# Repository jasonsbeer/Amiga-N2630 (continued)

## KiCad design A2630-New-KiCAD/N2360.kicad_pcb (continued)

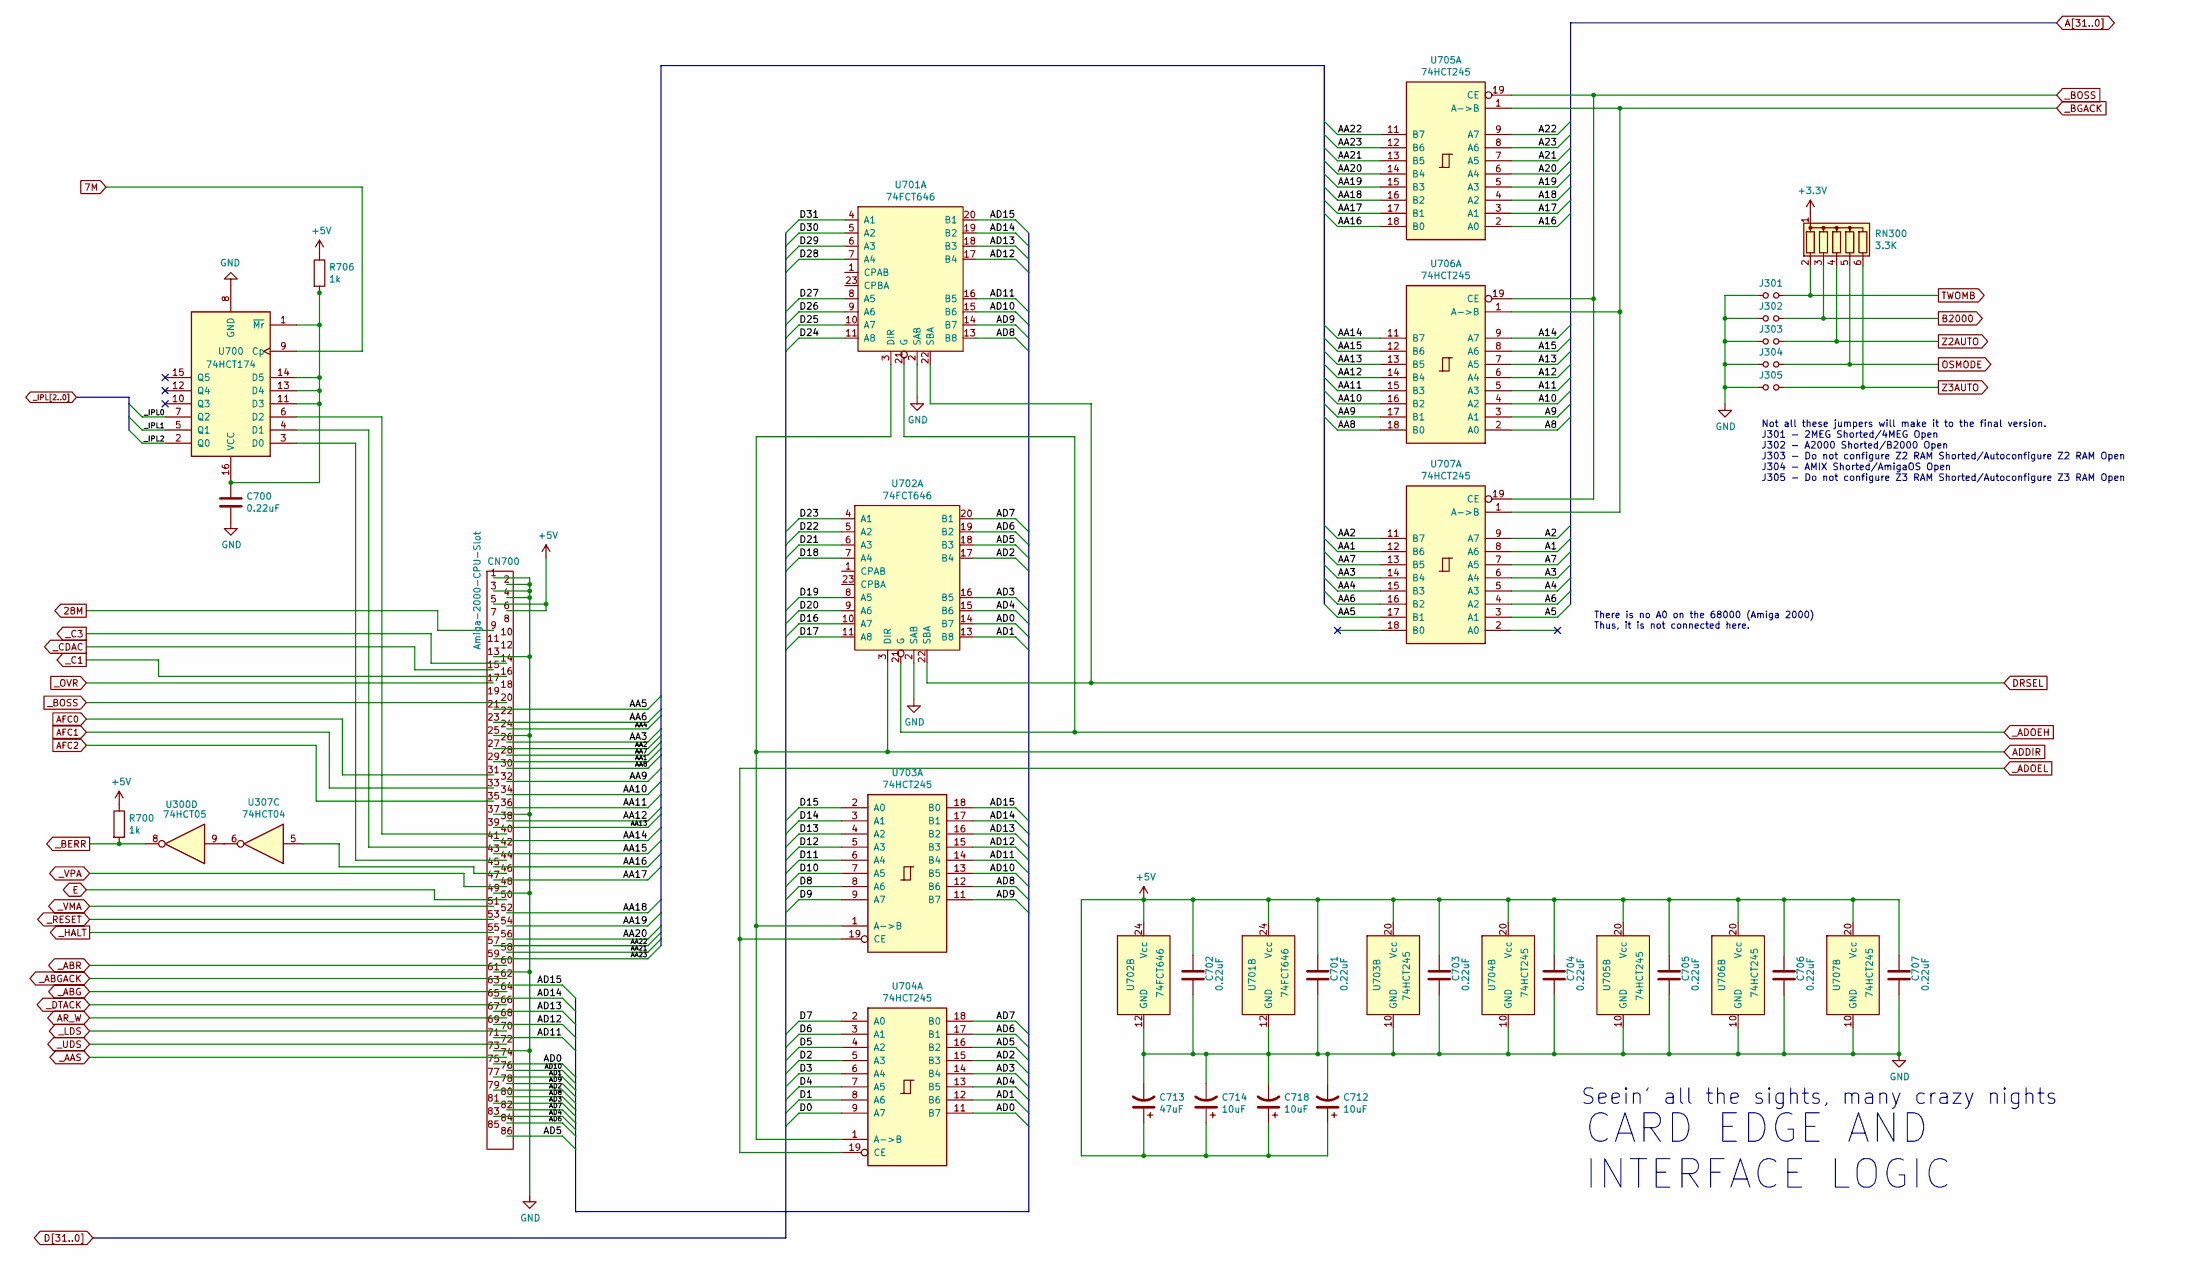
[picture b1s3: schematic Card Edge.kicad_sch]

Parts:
C700, C701, C702, C703, C704, C705, C706, C707: 0.22uF; C_0805_2012Metric
C712, C714, C718: 10uF; CP_Radial_D5.0mm_P2.00mm
C713: 47uF; CP_Radial_D5.0mm_P2.00mm
CN700: Amiga-2000-CPU-Slot; A2000_CPUSLOT_MALE
J301, J302, J303, J304, J305: Jumper_NO_Small; PinHeader_1x02_P2.54mm_Vertical
R700, R706: 1k; R_0805_2012Metric
RN300: 3.3K; R_Array_SIP6
U300: 74HCT05; SOIC-14_3.9x8.7mm_P1.27mm
U307: 74HCT04; SOIC-14_3.9x8.7mm_P1.27mm
U700: 74HCT174; SOIC-16_3.9x9.9mm_P1.27mm
U701, U702: 74FCT646; SOIC-24W_7.5x15.4mm_P1.27mm; Digikey 296-33244-5-ND
U703, U704, U705, U706, U707: 74HCT245; SOIC-24W_7.5x15.4mm_P1.27mm

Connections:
7M: U700.9 (Cp); also elsewhere on the board
28M: CN700.9; also elsewhere on the board
+3V3: RN300.1 (common); also elsewhere on the board
/Card Edge/AA1: CN700.29, U707.12 (B6)
/Card Edge/AA2: CN700.27, U707.11 (B7)
/Card Edge/AA3: CN700.26, U707.14 (B4)
/Card Edge/AA4: CN700.24, U707.15 (B3)
/Card Edge/AA5: CN700.21, U707.17 (B1)
/Card Edge/AA6: CN700.23, U707.16 (B2)
/Card Edge/AA7: CN700.28, U707.13 (B5)
/Card Edge/AA8: CN700.30, U706.18 (B0)
/Card Edge/AA9: CN700.32, U706.17 (B1)
/Card Edge/AA10: CN700.34, U706.16 (B2)
/Card Edge/AA11: CN700.36, U706.15 (B3)
/Card Edge/AA12: CN700.38, U706.14 (B4)
/Card Edge/AA13: CN700.39, U706.13 (B5)
/Card Edge/AA14: CN700.41, U706.11 (B7)
/Card Edge/AA15: CN700.43, U706.12 (B6)
/Card Edge/AA16: CN700.45, U705.18 (B0)
/Card Edge/AA17: CN700.47, U705.17 (B1)
/Card Edge/AA18: CN700.52, U705.16 (B2)
/Card Edge/AA19: CN700.54, U705.15 (B3)
/Card Edge/AA20: CN700.56, U705.14 (B4)
/Card Edge/AA21: CN700.58, U705.13 (B5)
/Card Edge/AA22: CN700.57, U705.11 (B7)
/Card Edge/AA23: CN700.59, U705.12 (B6)
/Card Edge/AD0: CN700.75, U702.14 (B7), U704.11 (B7)
/Card Edge/AD1: CN700.77, U702.13 (B8), U704.12 (B6)
/Card Edge/AD2: CN700.79, U702.17 (B4), U704.15 (B3)
/Card Edge/AD3: CN700.81, U702.16 (B5), U704.14 (B4)
/Card Edge/AD4: CN700.83, U702.15 (B6), U704.13 (B5)
/Card Edge/AD5: CN700.86, U702.18 (B3), U704.16 (B2)
/Card Edge/AD6: CN700.84, U702.19 (B2), U704.17 (B1)
/Card Edge/AD7: CN700.82, U702.20 (B1), U704.18 (B0)
/Card Edge/AD8: CN700.80, U701.13 (B8), U703.12 (B6)
/Card Edge/AD9: CN700.78, U701.14 (B7), U703.11 (B7)
/Card Edge/AD10: CN700.76, U701.15 (B6), U703.13 (B5)
/Card Edge/AD11: CN700.71, U701.16 (B5), U703.14 (B4)
/Card Edge/AD12: CN700.69, U701.17 (B4), U703.15 (B3)
/Card Edge/AD13: CN700.67, U701.18 (B3), U703.16 (B2)
/Card Edge/AD14: CN700.65, U701.19 (B2), U703.17 (B1)
/Card Edge/AD15: CN700.63, U701.20 (B1), U703.18 (B0)
A1: U707.8 (A6); also elsewhere on the board
A2: U707.9 (A7); also elsewhere on the board
A3: U707.6 (A4); also elsewhere on the board
A4: U707.5 (A3); also elsewhere on the board
A5: U707.3 (A1); also elsewhere on the board
A6: U707.4 (A2); also elsewhere on the board
A7: U707.7 (A5); also elsewhere on the board
A8: U706.2 (A0); also elsewhere on the board
A9: U706.3 (A1); also elsewhere on the board
A10: U706.4 (A2); also elsewhere on the board
A11: U706.5 (A3); also elsewhere on the board
A12: U706.6 (A4); also elsewhere on the board
A13: U706.7 (A5); also elsewhere on the board
A14: U706.9 (A7); also elsewhere on the board
A15: U706.8 (A6); also elsewhere on the board
A16: U705.2 (A0); also elsewhere on the board
A17: U705.3 (A1); also elsewhere on the board
A18: U705.4 (A2); also elsewhere on the board
A19: U705.5 (A3); also elsewhere on the board
A20: U705.6 (A4); also elsewhere on the board
A21: U705.7 (A5); also elsewhere on the board
A22: U705.9 (A7); also elsewhere on the board
A23: U705.8 (A6); also elsewhere on the board
ADDIR: U701.3 (DIR), U702.3 (DIR), U703.1 (A->B), U704.1 (A->B); also elsewhere on the board
AFC0: CN700.31; also elsewhere on the board
AFC1: CN700.33; also elsewhere on the board
AFC2: CN700.35; also elsewhere on the board
AR_W: CN700.68; also elsewhere on the board
B2000: J302.2, RN300.3 (R2); also elsewhere on the board
D0: U704.9 (A7); also elsewhere on the board
D1: U704.8 (A6); also elsewhere on the board
D2: U704.5 (A3); also elsewhere on the board
D3: U704.6 (A4); also elsewhere on the board
D4: U704.7 (A5); also elsewhere on the board
D5: U704.4 (A2); also elsewhere on the board
D6: U704.3 (A1); also elsewhere on the board
D7: U704.2 (A0); also elsewhere on the board
D8: U703.8 (A6); also elsewhere on the board
D9: U703.9 (A7); also elsewhere on the board
D10: U703.7 (A5); also elsewhere on the board
D11: U703.6 (A4); also elsewhere on the board
D12: U703.5 (A3); also elsewhere on the board
D13: U703.4 (A2); also elsewhere on the board
D14: U703.3 (A1); also elsewhere on the board
D15: U703.2 (A0); also elsewhere on the board
D16: U702.10 (A7); also elsewhere on the board
D17: U702.11 (A8); also elsewhere on the board
D18: U702.7 (A4); also elsewhere on the board
D19: U702.8 (A5); also elsewhere on the board
D20: U702.9 (A6); also elsewhere on the board
D21: U702.6 (A3); also elsewhere on the board
D22: U702.5 (A2); also elsewhere on the board
D23: U702.4 (A1); also elsewhere on the board
D24: U701.11 (A8); also elsewhere on the board
D25: U701.10 (A7); also elsewhere on the board
D26: U701.9 (A6); also elsewhere on the board
D27: U701.8 (A5); also elsewhere on the board
D28: U701.7 (A4); also elsewhere on the board
D29: U701.6 (A3); also elsewhere on the board
D30: U701.5 (A2); also elsewhere on the board
D31: U701.4 (A1); also elsewhere on the board
DRSEL: U701.22 (SBA), U702.22 (SBA); also elsewhere on the board
E: CN700.50; also elsewhere on the board
unnamed: C700.1, R706.2, U700.1 (~Mr), U700.11 (D3), U700.13 (D4), U700.14 (D5), U700.16 (VCC)
unnamed: CN700.40, U700.6 (D2)
unnamed: CN700.42, U700.4 (D1)
unnamed: CN700.44, U700.3 (D0)
unnamed: CN700.46, U307.5
unnamed: U300.9, U307.6
OSMODE: J304.2, RN300.5 (R4); also elsewhere on the board
TWOMB: J301.2, RN300.2 (R1); also elsewhere on the board
Z2AUTO: J303.2, RN300.4 (R3)
Z3AUTO: J305.2, RN300.6 (R5); also elsewhere on the board
_AAS: CN700.74; also elsewhere on the board
_ABG: CN700.64; also elsewhere on the board
_ABGACK: CN700.62; also elsewhere on the board
_ABR: CN700.60; also elsewhere on the board
_ADOEH: U701.21 (G), U702.21 (G); also elsewhere on the board
_ADOEL: U703.19 (CE), U704.19 (CE); also elsewhere on the board
_BERR: R700.2, U300.8; also elsewhere on the board
_BGACK: U705.1 (A->B), U706.1 (A->B), U707.1 (A->B); also elsewhere on the board
_BOSS: CN700.20, U705.19 (CE), U706.19 (CE), U707.19 (CE); also elsewhere on the board
_C1: CN700.16; also elsewhere on the board
_C3: CN700.14; also elsewhere on the board
_CDAC: CN700.15
_DTACK: CN700.66; also elsewhere on the board
_HALT: CN700.55; also elsewhere on the board
_IPL0: U700.7 (Q2); also elsewhere on the board
_IPL1: U700.5 (Q1); also elsewhere on the board
_IPL2: U700.2 (Q0); also elsewhere on the board
_LDS: CN700.70; also elsewhere on the board
_OVR: CN700.17; also elsewhere on the board
_RESET: CN700.53; also elsewhere on the board
_UDS: CN700.72; also elsewhere on the board
_VMA: CN700.51; also elsewhere on the board
_VPA: CN700.48; also elsewhere on the board

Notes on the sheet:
Seein' all the sights, many crazy nights
Not all these jumpers will make it to the final version. J301 - 2MEG Shorted/4MEG Open J302 - A2000 Shorted/B2000 Open J303 - Do not configure Z2 RAM Shorted/Autoconfigure Z2 RAM Open J304 - AMIX Shorted/AmigaOS Open J305 - Do not configure Z3 RAM Shorted/Autoconfigure Z3 RAM Open
There is no A0 on the 68000 (Amiga 2000) Thus, it is not connected here.
CARD EDGE AND INTERFACE LOGIC

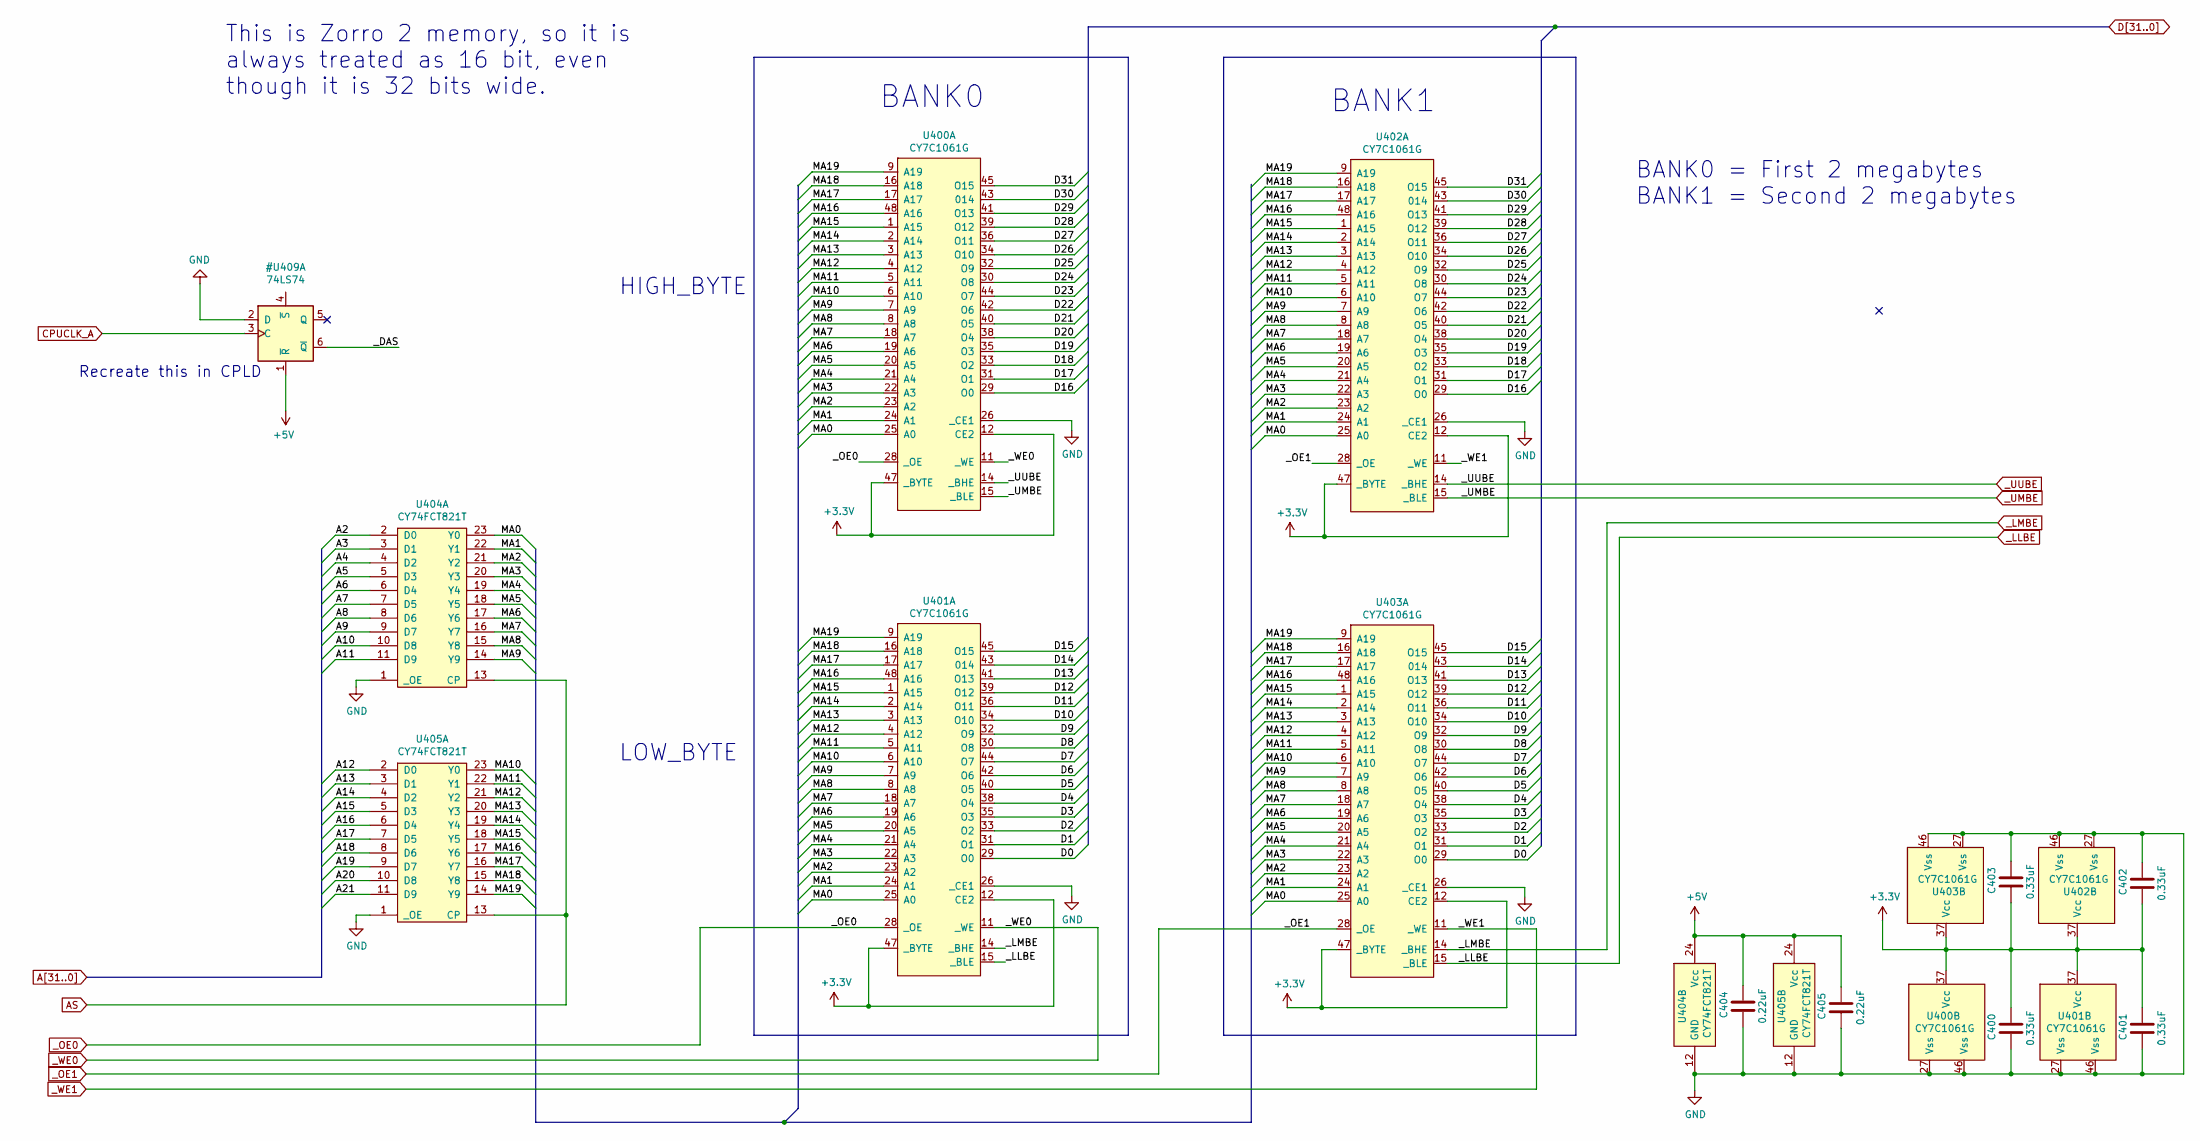
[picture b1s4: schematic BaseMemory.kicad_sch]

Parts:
C400, C401, C402, C403: 0.33uF; C_0805_2012Metric
C404, C405: 0.22uF; C_0805_2012Metric
U400, U401, U402, U403: CY7C1061G; TSOP-I-48_18.4x12mm_P0.5mm
U404, U405: CY74FCT821T; SOIC-24W_7.5x15.4mm_P1.27mm

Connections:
+3V3: C400.1, C401.1, C402.2, C403.2, U400.12 (CE2), U400.37 (Vcc), U400.47 (_BYTE), U401.12 (CE2), U401.37 (Vcc), U401.47 (_BYTE), U402.12 (CE2), U402.37 (Vcc), U402.47 (_BYTE), U403.12 (CE2), U403.37 (Vcc), U403.47 (_BYTE); also elsewhere on the board
/Base Memory/MA0: U400.25 (A0), U401.25 (A0), U402.25 (A0), U403.25 (A0), U404.23 (Y0)
/Base Memory/MA1: U400.24 (A1), U401.24 (A1), U402.24 (A1), U403.24 (A1), U404.22 (Y1)
/Base Memory/MA2: U400.23 (A2), U401.23 (A2), U402.23 (A2), U403.23 (A2), U404.21 (Y2)
/Base Memory/MA3: U400.22 (A3), U401.22 (A3), U402.22 (A3), U403.22 (A3), U404.20 (Y3)
/Base Memory/MA4: U400.21 (A4), U401.21 (A4), U402.21 (A4), U403.21 (A4), U404.19 (Y4)
/Base Memory/MA5: U400.20 (A5), U401.20 (A5), U402.20 (A5), U403.20 (A5), U404.18 (Y5)
/Base Memory/MA6: U400.19 (A6), U401.19 (A6), U402.19 (A6), U403.19 (A6), U404.17 (Y6)
/Base Memory/MA7: U400.18 (A7), U401.18 (A7), U402.18 (A7), U403.18 (A7), U404.16 (Y7)
/Base Memory/MA8: U400.8 (A8), U401.8 (A8), U402.8 (A8), U403.8 (A8), U404.15 (Y8)
/Base Memory/MA9: U400.7 (A9), U401.7 (A9), U402.7 (A9), U403.7 (A9), U404.14 (Y9)
/Base Memory/MA10: U400.6 (A10), U401.6 (A10), U402.6 (A10), U403.6 (A10), U405.23 (Y0)
/Base Memory/MA11: U400.5 (A11), U401.5 (A11), U402.5 (A11), U403.5 (A11), U405.22 (Y1)
/Base Memory/MA12: U400.4 (A12), U401.4 (A12), U402.4 (A12), U403.4 (A12), U405.21 (Y2)
/Base Memory/MA13: U400.3 (A13), U401.3 (A13), U402.3 (A13), U403.3 (A13), U405.20 (Y3)
/Base Memory/MA14: U400.2 (A14), U401.2 (A14), U402.2 (A14), U403.2 (A14), U405.19 (Y4)
/Base Memory/MA15: U400.1 (A15), U401.1 (A15), U402.1 (A15), U403.1 (A15), U405.18 (Y5)
/Base Memory/MA16: U400.48 (A16), U401.48 (A16), U402.48 (A16), U403.48 (A16), U405.17 (Y6)
/Base Memory/MA17: U400.17 (A17), U401.17 (A17), U402.17 (A17), U403.17 (A17), U405.16 (Y7)
/Base Memory/MA18: U400.16 (A18), U401.16 (A18), U402.16 (A18), U403.16 (A18), U405.15 (Y8)
/Base Memory/MA19: U400.9 (A19), U401.9 (A19), U402.9 (A19), U403.9 (A19), U405.14 (Y9)
A2: U404.2 (D0); also elsewhere on the board
A3: U404.3 (D1); also elsewhere on the board
A4: U404.4 (D2); also elsewhere on the board
A5: U404.5 (D3); also elsewhere on the board
A6: U404.6 (D4); also elsewhere on the board
A7: U404.7 (D5); also elsewhere on the board
A8: U404.8 (D6); also elsewhere on the board
A9: U404.9 (D7); also elsewhere on the board
A10: U404.10 (D8); also elsewhere on the board
A11: U404.11 (D9); also elsewhere on the board
A12: U405.2 (D0); also elsewhere on the board
A13: U405.3 (D1); also elsewhere on the board
A14: U405.4 (D2); also elsewhere on the board
A15: U405.5 (D3); also elsewhere on the board
A16: U405.6 (D4); also elsewhere on the board
A17: U405.7 (D5); also elsewhere on the board
A18: U405.8 (D6); also elsewhere on the board
A19: U405.9 (D7); also elsewhere on the board
A20: U405.10 (D8); also elsewhere on the board
A21: U405.11 (D9); also elsewhere on the board
AS: U404.13 (CP), U405.13 (CP); also elsewhere on the board
D0: U401.29 (O0), U403.29 (O0); also elsewhere on the board
D1: U401.31 (O1), U403.31 (O1); also elsewhere on the board
D2: U401.33 (O2), U403.33 (O2); also elsewhere on the board
D3: U401.35 (O3), U403.35 (O3); also elsewhere on the board
D4: U401.38 (O4), U403.38 (O4); also elsewhere on the board
D5: U401.40 (O5), U403.40 (O5); also elsewhere on the board
D6: U401.42 (O6), U403.42 (O6); also elsewhere on the board
D7: U401.44 (O7), U403.44 (O7); also elsewhere on the board
D8: U401.30 (O8), U403.30 (O8); also elsewhere on the board
D9: U401.32 (O9), U403.32 (O9); also elsewhere on the board
D10: U401.34 (O10), U403.34 (O10); also elsewhere on the board
D11: U401.36 (O11), U403.36 (O11); also elsewhere on the board
D12: U401.39 (O12), U403.39 (O12); also elsewhere on the board
D13: U401.41 (O13), U403.41 (O13); also elsewhere on the board
D14: U401.43 (014), U403.43 (014); also elsewhere on the board
D15: U401.45 (O15), U403.45 (O15); also elsewhere on the board
D16: U400.29 (O0), U402.29 (O0); also elsewhere on the board
D17: U400.31 (O1), U402.31 (O1); also elsewhere on the board
D18: U400.33 (O2), U402.33 (O2); also elsewhere on the board
D19: U400.35 (O3), U402.35 (O3); also elsewhere on the board
D20: U400.38 (O4), U402.38 (O4); also elsewhere on the board
D21: U400.40 (O5), U402.40 (O5); also elsewhere on the board
D22: U400.42 (O6), U402.42 (O6); also elsewhere on the board
D23: U400.44 (O7), U402.44 (O7); also elsewhere on the board
D24: U400.30 (O8), U402.30 (O8); also elsewhere on the board
D25: U400.32 (O9), U402.32 (O9); also elsewhere on the board
D26: U400.34 (O10), U402.34 (O10); also elsewhere on the board
D27: U400.36 (O11), U402.36 (O11); also elsewhere on the board
D28: U400.39 (O12), U402.39 (O12); also elsewhere on the board
D29: U400.41 (O13), U402.41 (O13); also elsewhere on the board
D30: U400.43 (014), U402.43 (014); also elsewhere on the board
D31: U400.45 (O15), U402.45 (O15); also elsewhere on the board
_LLBE: U401.15 (_BLE), U403.15 (_BLE); also elsewhere on the board
_LMBE: U401.14 (_BHE), U403.14 (_BHE); also elsewhere on the board
_OE0: U400.28 (_OE), U401.28 (_OE); also elsewhere on the board
_OE1: U402.28 (_OE), U403.28 (_OE); also elsewhere on the board
_UMBE: U400.15 (_BLE), U402.15 (_BLE); also elsewhere on the board
_UUBE: U400.14 (_BHE), U402.14 (_BHE); also elsewhere on the board
_WE0: U400.11 (_WE), U401.11 (_WE); also elsewhere on the board
_WE1: U402.11 (_WE), U403.11 (_WE); also elsewhere on the board

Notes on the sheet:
Recreate this in CPLD
BANK0 = First 2 megabytes BANK1 = Second 2 megabytes
This is Zorro 2 memory, so it is always treated as 16 bit, even though it is 32 bits wide.
BANK1
BANK0
HIGH_BYTE
LOW_BYTE

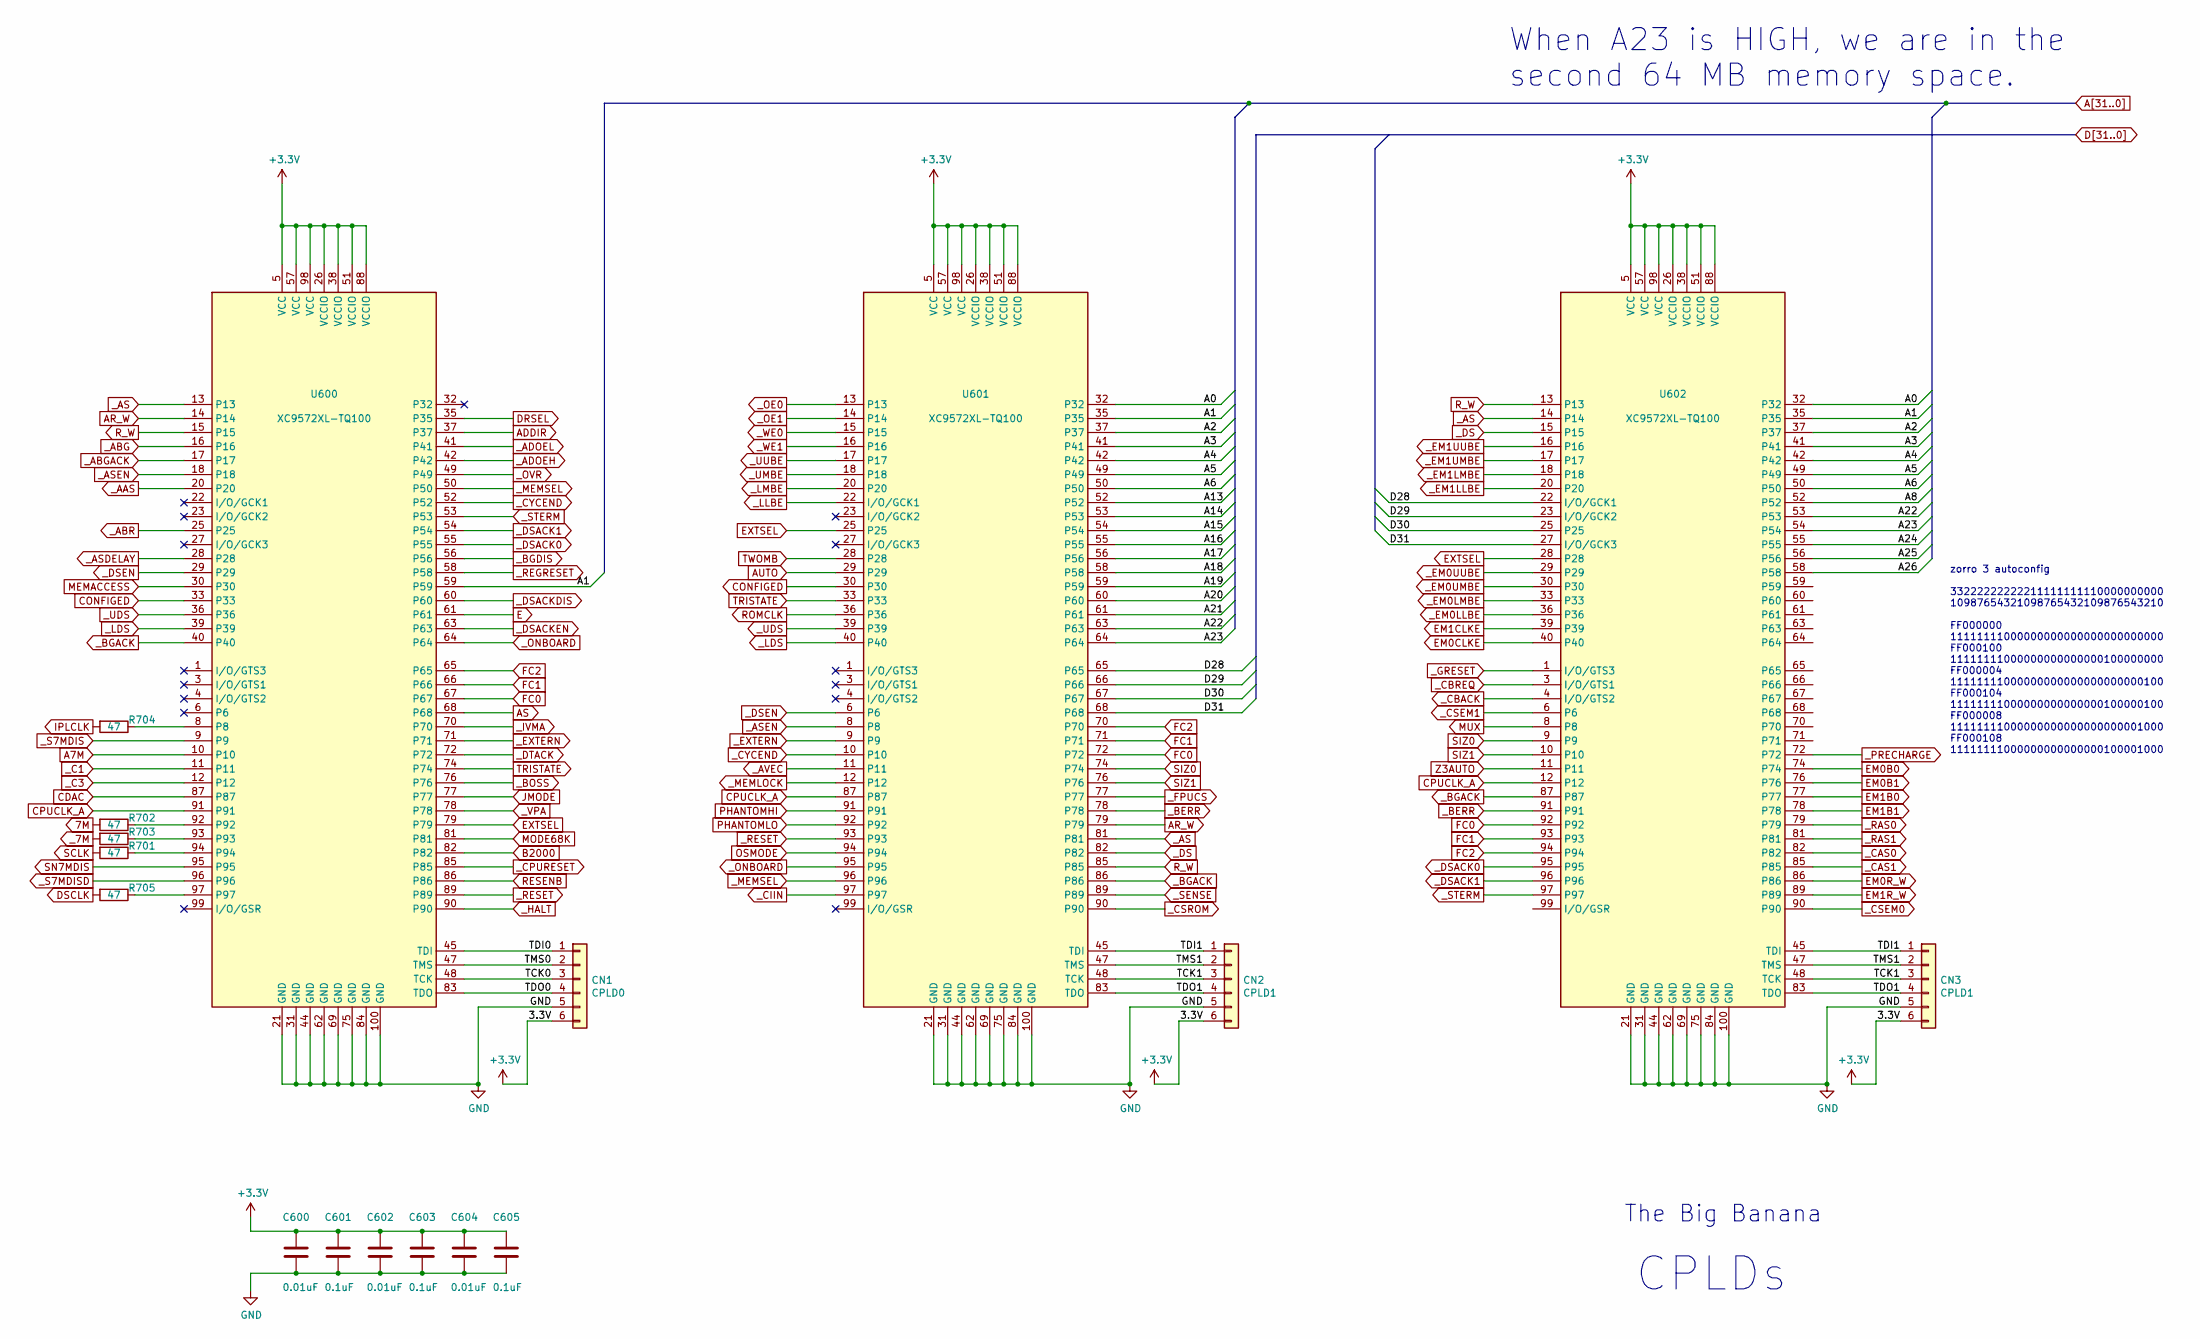
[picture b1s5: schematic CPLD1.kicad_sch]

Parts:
C600, C602, C604: 0.01uF; C_0805_2012Metric
C601, C603, C605: 0.1uF; C_0805_2012Metric
CN1: CPLD0; PinHeader_1x06_P2.54mm_Vertical
CN2, CN3: CPLD1; PinHeader_1x06_P2.54mm_Vertical
R701, R702, R703, R704, R705: 47; R_0805_2012Metric
U600, U601, U602: XC9572XL-TQ100; TQFP-100_14x14mm_P0.5mm

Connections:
7M: R702.2; also elsewhere on the board
+3V3: C600.1, C601.1, C602.1, C603.1, C604.1, C605.1, CN1.6, CN2.6, CN3.6, U600.5 (VCC), U600.26 (VCCIO), U600.38 (VCCIO), U600.51 (VCCIO), U600.57 (VCC), U600.88 (VCCIO), U600.98 (VCC), U601.5 (VCC), U601.26 (VCCIO), U601.38 (VCCIO), U601.51 (VCCIO), U601.57 (VCC), U601.88 (VCCIO), U601.98 (VCC), U602.5 (VCC), U602.26 (VCCIO), U602.38 (VCCIO), U602.51 (VCCIO), U602.57 (VCC), U602.88 (VCCIO), U602.98 (VCC); also elsewhere on the board
/CPLD 1/TCK0: CN1.3, U600.48 (TCK)
/CPLD 1/TCK1: CN2.3, CN3.3, U601.48 (TCK), U602.48 (TCK)
/CPLD 1/TDI0: CN1.1, U600.45 (TDI)
/CPLD 1/TDI1: CN2.1, CN3.1, U601.45 (TDI), U602.45 (TDI)
/CPLD 1/TDO0: CN1.4, U600.83 (TDO)
/CPLD 1/TDO1: CN2.4, CN3.4, U601.83 (TDO), U602.83 (TDO)
/CPLD 1/TMS0: CN1.2, U600.47 (TMS)
/CPLD 1/TMS1: CN2.2, CN3.2, U601.47 (TMS), U602.47 (TMS)
A0: U601.32, U602.32; also elsewhere on the board
A1: U600.59, U601.35, U602.35; also elsewhere on the board
A2: U601.37, U602.37; also elsewhere on the board
A3: U601.41, U602.41; also elsewhere on the board
A4: U601.42, U602.42; also elsewhere on the board
A5: U601.49, U602.49; also elsewhere on the board
A6: U601.50, U602.50; also elsewhere on the board
A7M: U600.10
A8: U602.52; also elsewhere on the board
A13: U601.52; also elsewhere on the board
A14: U601.53; also elsewhere on the board
A15: U601.54; also elsewhere on the board
A16: U601.55; also elsewhere on the board
A17: U601.56; also elsewhere on the board
A18: U601.58; also elsewhere on the board
A19: U601.59; also elsewhere on the board
A20: U601.60; also elsewhere on the board
A21: U601.61; also elsewhere on the board
A22: U601.63, U602.53; also elsewhere on the board
A23: U601.64, U602.54; also elsewhere on the board
A24: U602.55; also elsewhere on the board
A25: U602.56; also elsewhere on the board
A26: U602.58; also elsewhere on the board
ADDIR: U600.37; also elsewhere on the board
AR_W: U600.14, U601.79; also elsewhere on the board
AS: U600.68; also elsewhere on the board
AUTO: U601.29
B2000: U600.82; also elsewhere on the board
CDAC: U600.87
CONFIGED: U600.33, U601.30
CPUCLK_A: U600.91, U601.87, U602.12; also elsewhere on the board
D28: U601.65, U602.22 (I/O/GCK1); also elsewhere on the board
D29: U601.66, U602.23 (I/O/GCK2); also elsewhere on the board
D30: U601.67, U602.25; also elsewhere on the board
D31: U601.68, U602.27 (I/O/GCK3); also elsewhere on the board
DRSEL: U600.35; also elsewhere on the board
DSCLK: R705.2; also elsewhere on the board
E: U600.61; also elsewhere on the board
EM0B0: U602.74; also elsewhere on the board
EM0B1: U602.76; also elsewhere on the board
EM0CLKE: U602.40; also elsewhere on the board
EM0R_W: U602.86; also elsewhere on the board
EM1B0: U602.77; also elsewhere on the board
EM1B1: U602.78; also elsewhere on the board
EM1CLKE: U602.39; also elsewhere on the board
EM1R_W: U602.89; also elsewhere on the board
EXTSEL: U600.79, U601.25, U602.28; also elsewhere on the board
FC0: U600.67, U601.72, U602.92; also elsewhere on the board
FC1: U600.66, U601.71, U602.93; also elsewhere on the board
FC2: U600.65, U601.70, U602.94; also elsewhere on the board
IPLCLK: R704.2
JMODE: U600.77; also elsewhere on the board
MEMACCESS: U600.30
MODE68K: U600.81
MUX: U602.8; also elsewhere on the board
unnamed: R701.1, U600.94
unnamed: R702.1, U600.92
unnamed: R703.1, U600.93
unnamed: R704.1, U600.8
unnamed: R705.1, U600.97
OSMODE: U601.94; also elsewhere on the board
PHANTOMHI: U601.91; also elsewhere on the board
PHANTOMLO: U601.92; also elsewhere on the board
RESENB: U600.86
ROMCLK: U601.36; also elsewhere on the board
R_W: U600.15, U601.85, U602.13; also elsewhere on the board
SCLK: R701.2; also elsewhere on the board
SIZ0: U601.74, U602.9; also elsewhere on the board
SIZ1: U601.76, U602.10; also elsewhere on the board
SN7MDIS: U600.95
TRISTATE: U600.74, U601.33; also elsewhere on the board
TWOMB: U601.28; also elsewhere on the board
Z3AUTO: U602.11; also elsewhere on the board
_7M: R703.2
_AAS: U600.20; also elsewhere on the board
_ABG: U600.16; also elsewhere on the board
_ABGACK: U600.17; also elsewhere on the board
_ABR: U600.25; also elsewhere on the board
_ADOEH: U600.42; also elsewhere on the board
_ADOEL: U600.41; also elsewhere on the board
_AS: U600.13, U601.81, U602.14; also elsewhere on the board
_ASDELAY: U600.28; also elsewhere on the board
_ASEN: U600.18, U601.8; also elsewhere on the board
_AVEC: U601.11; also elsewhere on the board
_BERR: U601.78, U602.91; also elsewhere on the board
_BGACK: U600.40, U601.86, U602.87; also elsewhere on the board
_BGDIS: U600.56
_BOSS: U600.76; also elsewhere on the board
_C1: U600.11; also elsewhere on the board
_C3: U600.12; also elsewhere on the board
_CAS0: U602.82; also elsewhere on the board
_CAS1: U602.85; also elsewhere on the board
_CBACK: U602.4 (I/O/GTS2); also elsewhere on the board
_CBREQ: U602.3 (I/O/GTS1); also elsewhere on the board
_CIIN: U601.97; also elsewhere on the board
_CPURESET: U600.85; also elsewhere on the board
_CSEM0: U602.90
_CSEM1: U602.6
_CSROM: U601.90; also elsewhere on the board
_CYCEND: U600.52, U601.10
_DS: U601.82, U602.15; also elsewhere on the board
_DSACK0: U600.55, U602.95; also elsewhere on the board
_DSACK1: U600.54, U602.96; also elsewhere on the board
_DSACKDIS: U600.60; also elsewhere on the board
_DSACKEN: U600.63; also elsewhere on the board
_DSEN: U600.29, U601.6
_DTACK: U600.72; also elsewhere on the board
_EM0LLBE: U602.36; also elsewhere on the board
_EM0LMBE: U602.33; also elsewhere on the board
_EM0UMBE: U602.30; also elsewhere on the board
_EM0UUBE: U602.29; also elsewhere on the board
_EM1LLBE: U602.20; also elsewhere on the board
_EM1LMBE: U602.18; also elsewhere on the board
_EM1UMBE: U602.17; also elsewhere on the board
_EM1UUBE: U602.16; also elsewhere on the board
_EXTERN: U600.71, U601.9
_FPUCS: U601.77; also elsewhere on the board
_GRESET: U602.1 (I/O/GTS3); also elsewhere on the board
_HALT: U600.90; also elsewhere on the board
_IVMA: U600.70; also elsewhere on the board
_LDS: U600.39, U601.40; also elsewhere on the board
_LLBE: U601.22 (I/O/GCK1); also elsewhere on the board
_LMBE: U601.20; also elsewhere on the board
_MEMLOCK: U601.12; also elsewhere on the board
_MEMSEL: U600.50, U601.96; also elsewhere on the board
_OE0: U601.13; also elsewhere on the board
_OE1: U601.14; also elsewhere on the board
_ONBOARD: U600.64, U601.95
_OVR: U600.49; also elsewhere on the board
_PRECHARGE: U602.72; also elsewhere on the board
_RAS0: U602.79; also elsewhere on the board
_RAS1: U602.81; also elsewhere on the board
_REGRESET: U600.58; also elsewhere on the board
_RESET: U600.89, U601.93; also elsewhere on the board
_S7MDIS: U600.9; also elsewhere on the board
_S7MDISD: U600.96; also elsewhere on the board
_SENSE: U601.89; also elsewhere on the board
_STERM: U600.53, U602.97; also elsewhere on the board
_UDS: U600.36, U601.39; also elsewhere on the board
_UMBE: U601.18; also elsewhere on the board
_UUBE: U601.17; also elsewhere on the board
_VPA: U600.78; also elsewhere on the board
_WE0: U601.15; also elsewhere on the board
_WE1: U601.16; also elsewhere on the board

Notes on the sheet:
When A23 is HIGH, we are in the second 64 MB memory space.
CPLDs
The Big Banana
zorro 3 autoconfig 33222222222211111111110000000000 10987654321098765432109876543210 FF000000 11111111000000000000000000000000 FF000100 11111111000000000000000100000000 FF000004 11111111000000000000000000000100 FF000104 11111111000000000000000100000100 FF000008 11111111000000000000000000001000 FF00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
